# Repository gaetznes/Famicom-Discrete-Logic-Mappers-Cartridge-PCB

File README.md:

# Famicom-Discrete-Logic-Mappers-Cartridge-PCB

PCB for games that use discrete logic on the Famicom System

This board was ported over from Mousebitelabs NES board to a Famicom Board.

All I did was drag and drop the components, and do my best to make sure everything was connected.

This board has not been tested.

## Acknowledgements and Thanks goes to:

Mousebitelabs: Everything but the Cutline and Edge Connector: 
https://github.com/MouseBiteLabs/NES-Cartridges/tree/main/Discrete%20Logic%20Mappers

Gumball2415: Cutline and Edge Connector:
https://github.com/Gumball2415/NES-Famicom-Cartridge-PCBs/tree/main/unrom-board

Benhack: Conversion Table: 
https://www.benheck.com/Downloads/NES_Famicom_Pinouts.pdf

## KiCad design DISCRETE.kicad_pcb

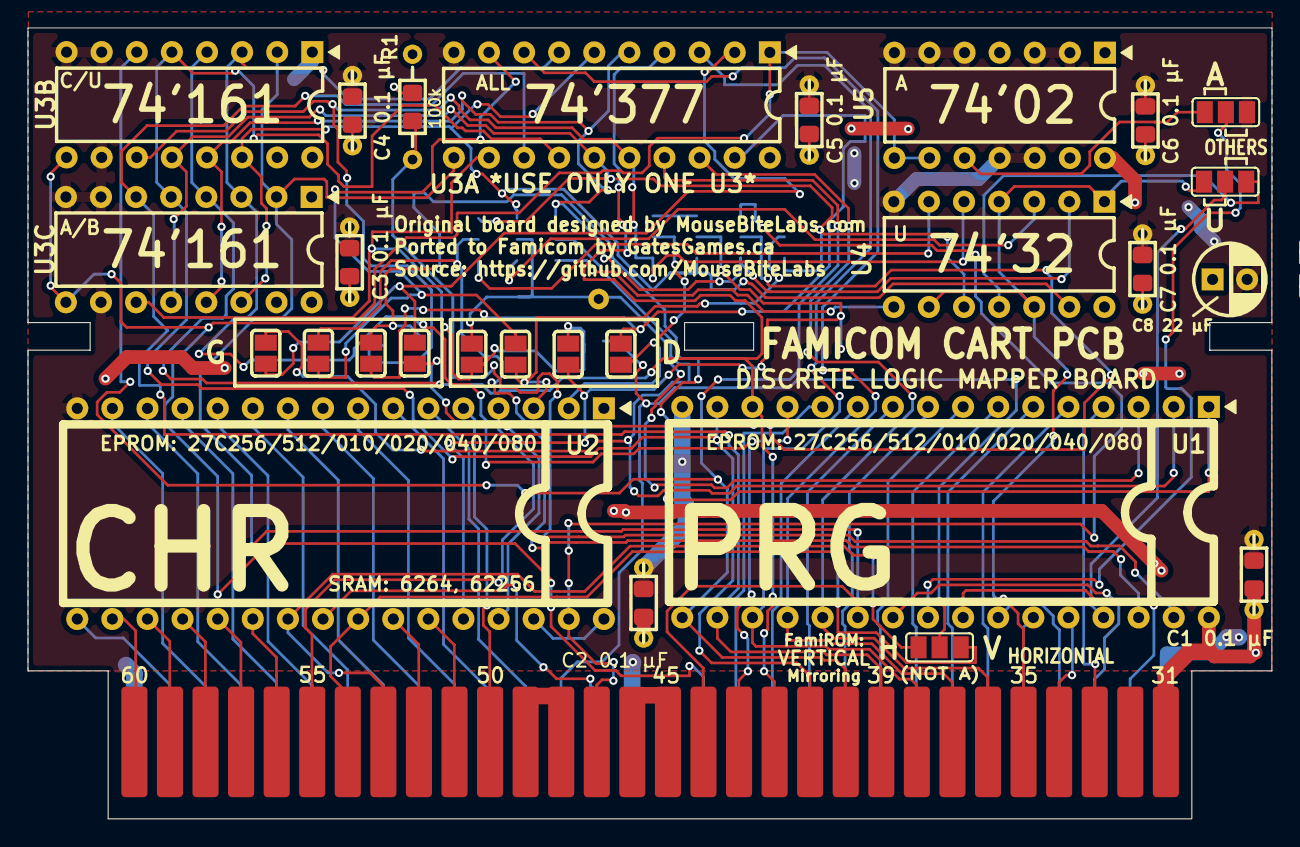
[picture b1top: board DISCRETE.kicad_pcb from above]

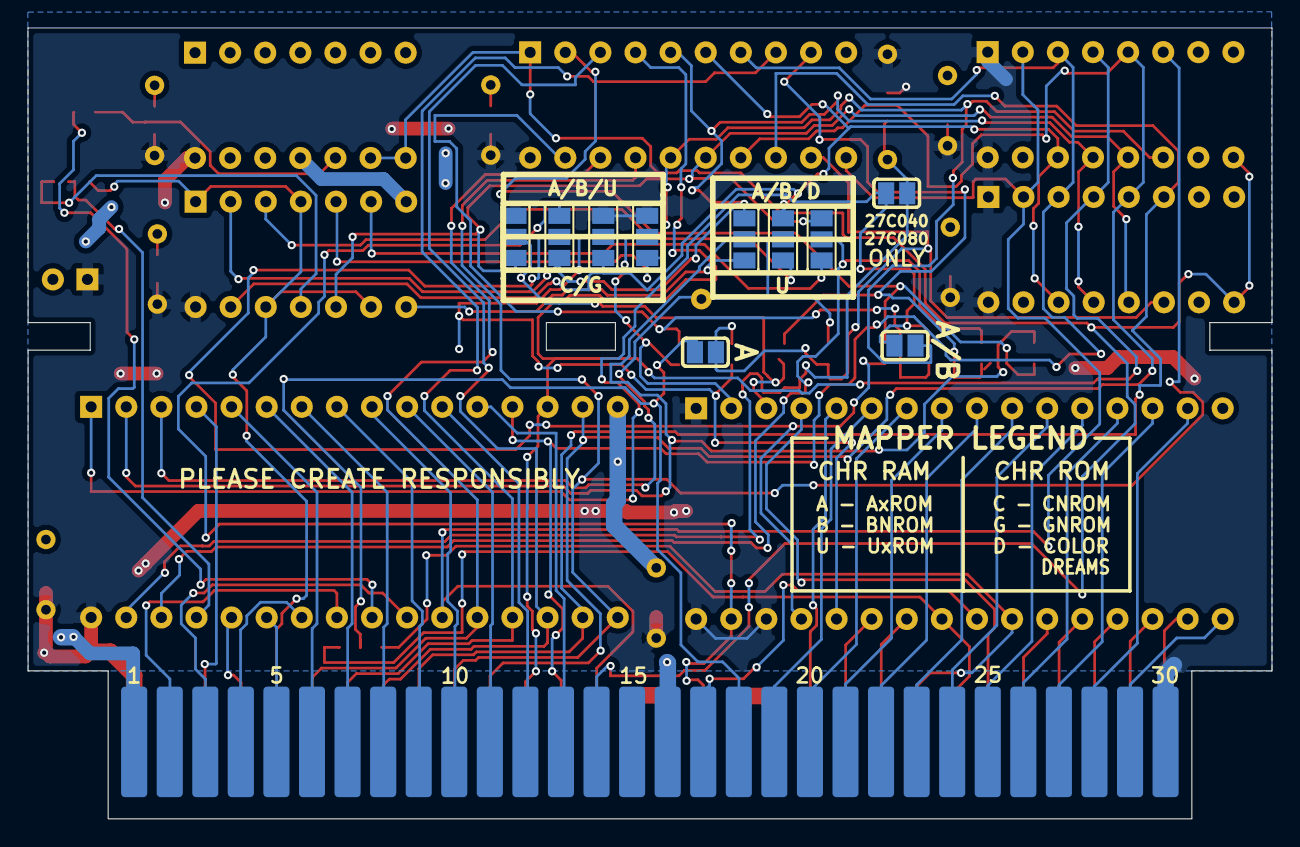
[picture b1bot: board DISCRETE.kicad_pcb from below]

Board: 2 copper layers, 90.0 x 57.2 mm, 39 parts (10 on the bottom side), 78 nets.

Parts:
C1 0.1 µF , C3 0.1 µF , C4 0.1 µF , C5 0.1 µF , C6 0.1 µF , C7 0.1 µF : 0.1u; THT_SMT_0803_SHORT
C4A: C2 0.1 µF; THT_SMT_0803_SHORT
C8 22 µF : 22u; CP_Radial_D5.0mm_P2.50mm
JP1, JP2, JP3, JP9, JP10, JP11, JP13, JP14, JP15, JP16: Jumper_3_Open; SJ_2
JP4, JP5, JP6, JP7, JP8, JP12, JP17, JP18, JP19, JP20, JP21: Jumper_2_Open; SJ
R1: 100k; THT_SMT_0803
TP2: TestPoint; TestPoint_THTPad_D1.5mm_Drill0.7mm
U2: 39SF040; DIP-32_W15.24mm
U3: 39SF040/6264; DIP-32_W15.24mm
U3A: 74LS377; DIP-20_W7.62mm
U3B, U3C: 74LS161; DIP-16_W7.62mm
U4: 74LS32; DIP-14_W7.62mm
U5: Famicom_Cart_Port; Famicom_connector
U5#2: 74LS02; DIP-14_W7.62mm

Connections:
+5V: C1 0.1 µF.1, C3 0.1 µF.1, C4 0.1 µF.1, C4A.1, C5 0.1 µF.1, C6 0.1 µF.1, C7 0.1 µF.1, C8 22 µF.1, JP13.3 (B), JP15.3 (B), JP16.3 (B), R1.1, U2.32 (VCC), U3.1 (A18), U3.30 (A17/VCC), U3.32 (VCC), U3A.20 (VCC), U3B.1 (~MR), U3B.16 (VCC), U3C.1 (~MR), U3C.16 (VCC), U4.14 (VCC), U5.30 (+5V), U5.31 (+5V), U5#2.14 (VCC)
/AA13: JP13.2 (C), JP17.1 (A), U3.28 (A13/CS2)
/AA14: JP14.2 (C), JP18.1 (A), U3.29 (A14/~WE)
/AA15: JP15.2 (C), JP19.1 (A), U3.3 (A15)
/AA16: JP16.2 (C), JP20.1 (A), U3.2 (A16)
/A_{0}: U2.12 (A0), U5.13 (CPU_A0)
/A_{1}: U2.11 (A1), U5.12 (CPU_A1)
/A_{2}: U2.10 (A2), U5.11 (CPU_A2)
/A_{3}: U2.9 (A3), U5.10 (CPU_A3)
/A_{4}: U2.8 (A4), U5.9
/A_{5}: U2.7 (A5), U5.8
/A_{6}: U2.6 (A6), U5.7
/A_{7}: U2.5 (A7), U5.6
/A_{8}: U2.27 (A8), U5.5
/A_{9}: U2.26 (A9), U5.4
/A_{10}: U2.23 (A10), U5.3
/A_{11}: U2.25 (A11), U5.2
/A_{12}: U2.4 (A12), U5.33 (CPU_A12)
/A_{13}: U2.28 (A13), U5.34 (CPU_A13)
/A_{14}: JP1.3 (B), U4.1, U4.4, U4.9, U4.12, U5.35 (CPU_A14)
/D_{0}: U2.13 (D0), U3A.7 (D2), U3B.3 (D0), U3C.3 (D0), U5.43 (CPU_D0)
/D_{1}: U2.14 (D1), U3A.4 (D1), U3B.4 (D1), U3C.4 (D1), U5.42 (CPU_D1)
/D_{2}: U2.15 (D2), U3A.14 (D5), U3B.5 (D2), U3C.5 (D2), U5.41 (CPU_D2)
/D_{3}: U2.17 (D3), U3A.17 (D6), U3B.6 (D3), U5.40 (CPU_D3)
/D_{4}: U2.18 (D4), U3A.13 (D4), U3C.6 (D3), U5.39 (CPU_D4)
/D_{5}: U2.19 (D5), U3A.3 (D0), U5.38 (CPU_D5)
/D_{6}: U2.20 (D6), U3A.8 (D3), U5.37 (CPU_D6)
/D_{7}: U2.21 (D7), U3A.18 (D7), U5.36 (CPU_D7)
/EXP_{0}: JP21.1 (A), R1.2, U2.31 (~WE)
/PA_{0}: U3.12 (A0), U5.25 (PPU_A0)
/PA_{1}: U3.11 (A1), U5.24 (PPU_A1)
/PA_{2}: U3.10 (A2), U5.23 (PPU_A2)
/PA_{3}: U3.9 (A3), U5.22 (PPU_A3)
/PA_{4}: U3.8 (A4), U5.21 (PPU_A4)
/PA_{5}: U3.7 (A5), U5.20 (PPU_A5)
/PA_{6}: U3.6 (A6), U5.19 (PPU_A6)
/PA_{7}: U3.5 (A7), U5.50 (PPU_A7)
/PA_{8}: U3.27 (A8), U5.51 (PPU_A8)
/PA_{9}: U3.26 (A9), U5.52 (PPU_A9)
/PA_{10}: JP3.1 (A), U3.23 (A10), U5.53 (PPU_A10)
/PA_{11}: JP3.3 (B), U3.25 (A11), U5.54 (PPU_A11)
/PA_{12}: U3.4 (A12), U5.55 (PPU_A12)
/PA_{13}: U3.22 (~CE), U5.56 (PPU_A13)
/PD_{0}: U3.13 (D0), U5.26 (PPU_D0)
/PD_{1}: U3.14 (D1), U5.27 (PPU_D1)
/PD_{2}: U3.15 (D2), U5.28 (PPU_D2)
/PD_{3}: U3.17 (D3), U5.29 (PPU_D3)
/PD_{4}: U3.18 (D4), U5.60 (PPU_D4)
/PD_{5}: U3.19 (D5), U5.59 (PPU_D5)
/PD_{6}: U3.20 (D6), U5.58 (PPU_D6)
/PD_{7}: U3.21 (D7), U5.57 (PPU_D7)
/Q_{0U}: JP1.1 (A), U4.11
/Q_{0}: JP9.1 (A), JP13.1 (A), U3A.6 (Q2), U3B.14 (Q0), U3C.14 (Q0), U4.13
/Q_{1U}: JP9.3 (B), U4.3
/Q_{1}: JP10.1 (A), JP14.1 (A), U3A.5 (Q1), U3B.13 (Q1), U3C.13 (Q1), U4.2
/Q_{2U}: JP10.3 (B), U4.8
/Q_{2}: JP11.1 (A), JP15.1 (A), U3A.15 (Q5), U3B.12 (Q2), U3C.12 (Q2), U4.10
/Q_{3U}: JP11.3 (B), U4.6
/Q_{3}: JP12.2 (B), JP16.1 (A), U3A.16 (Q6), U3B.11 (Q3), U4.5
/Q_{4}: JP4.2 (B), JP5.1 (A), JP17.2 (B), U3A.12 (Q4), U3C.11 (Q3)
/Q_{5}: JP6.1 (A), JP18.2 (B), U3A.2 (Q0)
/Q_{6}: JP7.1 (A), JP19.2 (B), U3A.9 (Q3)
/Q_{7}: JP8.1 (A), JP20.2 (B), U3A.19 (Q7)
/RA_{14}: JP1.2 (C), U2.29 (A14)
/RA_{15}: JP5.2 (B), JP9.2 (C), TP2.1, U2.3 (A15)
/RA_{16}: JP6.2 (B), JP10.2 (C), U2.2 (A16)
/RA_{17}: JP7.2 (B), JP11.2 (C), U2.30 (A17)
/RA_{18}: JP8.2 (B), JP12.1 (A), JP21.2 (B), U2.1 (A18)
/R/~W: U3A.1 (~E), U3B.9 (~PE), U3C.9 (~PE), U5.14 (CPU_R/W), U5#2.8, U5#2.9
/VRAM_{A10}: JP3.2 (C), JP4.1 (A), U5.18 (CIRAM_A10)
/~OE_{PRG}: JP2.2 (C), U2.24 (~OE)
/~PRD: U3.24 (~OE), U5.17 (PPU_/RD)
/~PWR: JP14.3 (B), U3.31 (~WE), U5.47 (PPU_/WR)
/~ROMSEL: U2.22 (~CE), U3A.11 (CP), U3B.2 (CP), U3C.2 (CP), U5.44 (/ROMSEL)
GND: C1 0.1 µF.2, C3 0.1 µF.2, C4 0.1 µF.2, C4A.2, C5 0.1 µF.2, C6 0.1 µF.2, C7 0.1 µF.2, C8 22 µF.2, JP2.1 (A), U2.16 (GND), U3.16 (GND), U3A.10 (GND), U3B.7 (CEP), U3B.8 (GND), U3B.10 (CET), U3C.7 (CEP), U3C.8 (GND), U3C.10 (CET), U4.7 (GND), U5.1, U5.16 (GND), U5#2.2, U5#2.3, U5#2.5, U5#2.6, U5#2.7 (GND), U5#2.11, U5#2.12
unnamed: JP2.3 (B), U5#2.10
unnamed: U5.45 (AUDIO_IN), U5.46 (AUDIO_OUT)
unnamed: U5.48 (CIRAM_/CE), U5.49 (PPU_/A13)
